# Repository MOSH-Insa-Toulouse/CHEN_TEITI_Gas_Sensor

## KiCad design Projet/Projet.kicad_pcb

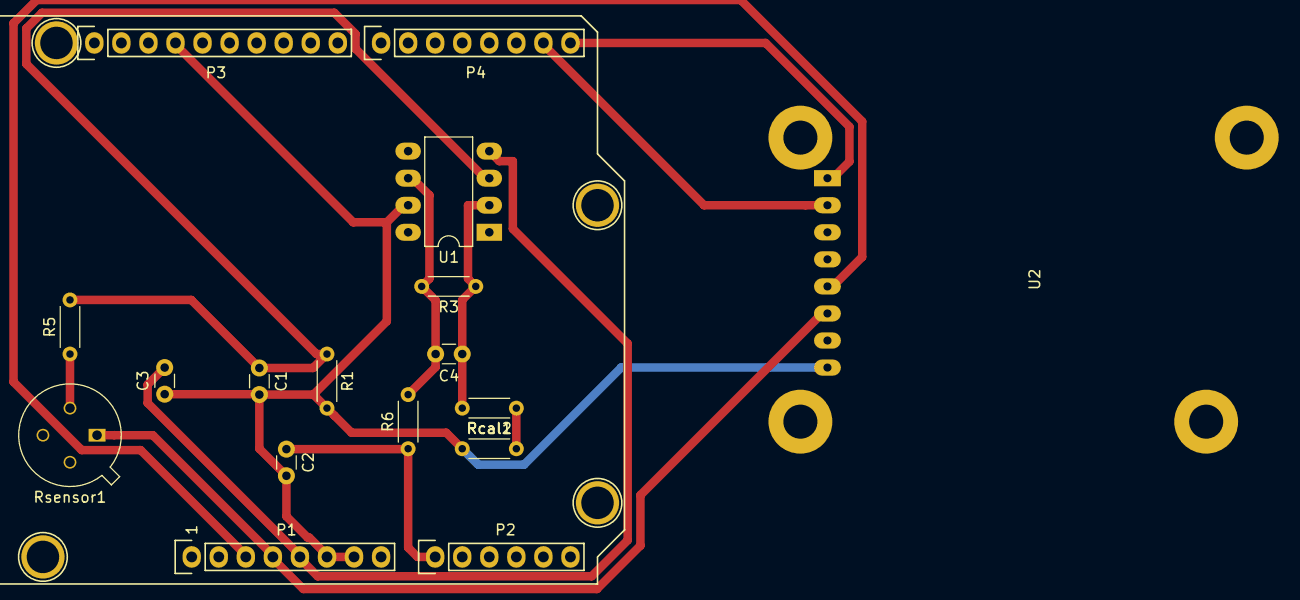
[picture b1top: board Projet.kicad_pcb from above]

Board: 2 copper layers, 21 parts (0 on the bottom side), 14 nets.

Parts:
C1, C2, C3: 100n; C_Disc_D3.0mm_W1.6mm_P2.50mm
C4: 1u; C_Disc_D3.0mm_W1.6mm_P2.50mm
P1: Power; Socket_Strip_Arduino_1x08
P2: Analog; Socket_Strip_Arduino_1x06
P3: Digital; Socket_Strip_Arduino_1x10
P4: Digital; Socket_Strip_Arduino_1x08
P5, P6, P7, P8: CONN_01X01; Arduino_1pin
R1, R3: 100k; R_Axial_DIN0204_L3.6mm_D1.6mm_P5.08mm_Horizontal
R5: 10k; R_Axial_DIN0204_L3.6mm_D1.6mm_P5.08mm_Horizontal
R6: 1k; R_Axial_DIN0204_L3.6mm_D1.6mm_P5.08mm_Horizontal
Rcal1, Rcal2: R; R_Axial_DIN0204_L3.6mm_D1.6mm_P5.08mm_Horizontal
Rsensor1: 10k<...<1G; TO-5-4
U1: LTC1050; DIP-8_W7.62mm_LongPads
U2: RN2483_Breakout; Modul_RN2483_Breakout

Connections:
+3V3: P1.4, Rsensor1.1, U2.6
+5V: C3.2, P1.5, U1.4
/0(Rx): P4.8, U2.1
/1(Tx): P4.7, U2.2
/A0: C2.1, P2.1, R6.1
/A4(SDA): P2.5, P3.2
/A5(SCL): P2.6, P3.1
/Reset: P1.3, U2.5
GND: C1.2, C2.2, C3.1, P1.6, P1.7, P3.4, R1.2, Rcal2.1, U1.7, U2.8
unnamed: C1.1, R1.1, R5.2, U1.3
unnamed: C4.1, R3.1, Rcal1.2, U1.2
unnamed: C4.2, R3.2, R6.2, U1.6
unnamed: R5.1, Rsensor1.2
unnamed: Rcal1.1, Rcal2.2

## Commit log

2018-11-28 init commit
2018-11-28 Add project
2018-11-28 fix readme
